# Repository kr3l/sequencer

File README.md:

ESP32 + TL074

the TL074 opamp is fed with -12 and +12V

GPIO25 -> pin3 of opamp
5.6kOhm + 1kOhm precision trimmer between pin 1 and 2 of opamp (feedback resistor)
10kOhm resistor between pin 2 and GND
-> opamp gain 1 + 5.6/10 -> 1.56
-> output max goes from 3.3V to 5.148V

100nF between pin 1 and GND

precision trimmer calibrated so the max outputted voltage on DAC results in exactly 5V

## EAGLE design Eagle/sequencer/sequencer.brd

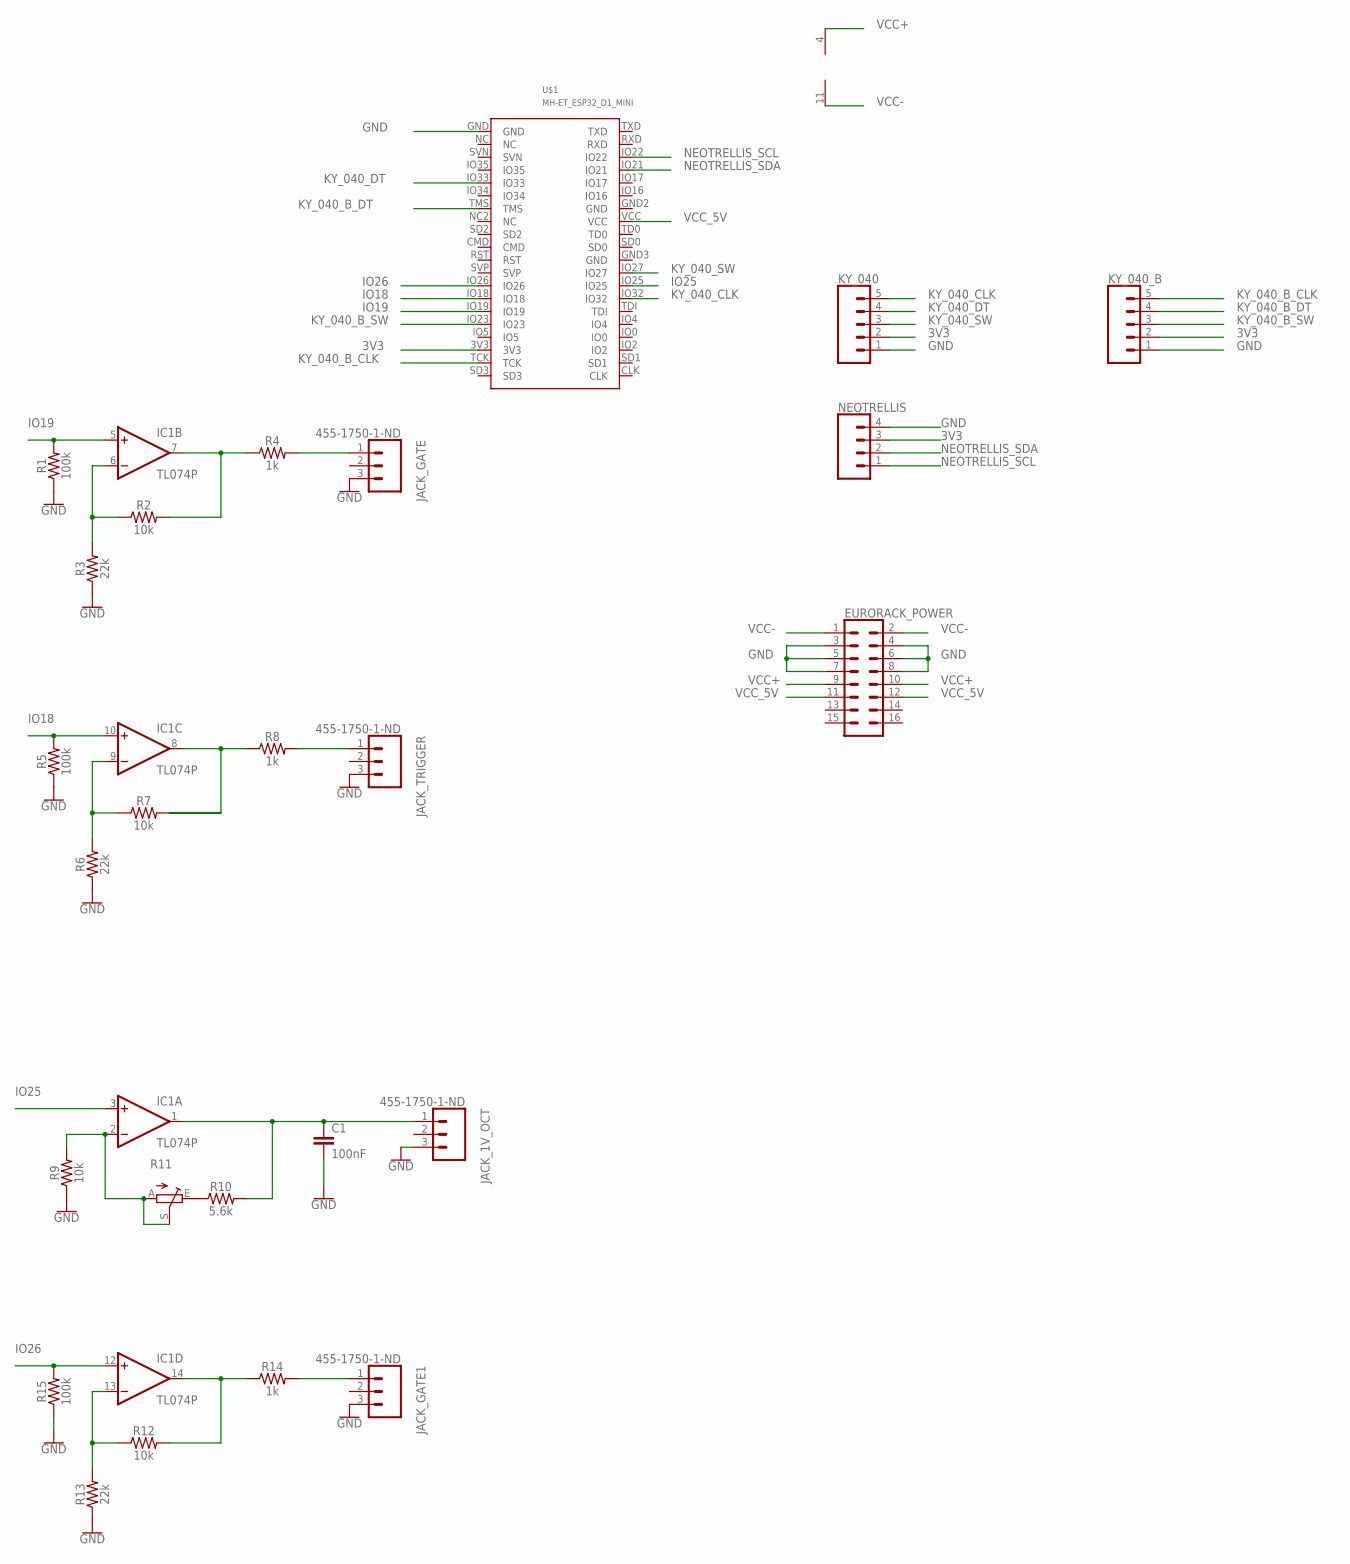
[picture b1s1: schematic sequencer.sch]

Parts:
C1: 100nF; C050-035X075
EURORACK_POWER: CONN_08X2_SHROUD; 2X8-SHROUDED_LOCK
IC1: TL074P; DIL14
JACK_1V_OCT: 455-1750-1-ND; 1X03
JACK_GATE, JACK_GATE1: 455-1750-1-ND; 1X03
JACK_TRIGGER: 455-1750-1-ND; 1X03
KY_040, KY_040_B: CONN_05; 1X05
NEOTRELLIS: CONN_04PTH; 1X04
R1, R5, R15: 100k; AXIAL-0.1
R2, R7, R9, R12: 10k; AXIAL-0.1
R3, R6, R13: 22k; AXIAL-0.1
R4, R8, R14: 1k; AXIAL-0.1
R10: 5.6k; AXIAL-0.1
R11: TRIM_EU-B64W; B64W
U$1: MH-ET_ESP32_D1_MINI

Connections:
3V3: KY_040.2, KY_040_B.2, NEOTRELLIS.3, U$1.3V3
GND: C1.2, EURORACK_POWER.3, EURORACK_POWER.4, EURORACK_POWER.5, EURORACK_POWER.6, EURORACK_POWER.7, EURORACK_POWER.8, JACK_1V_OCT.3, JACK_GATE.3, JACK_GATE1.3, JACK_TRIGGER.3, KY_040.1, KY_040_B.1, NEOTRELLIS.4, R1.P$1 (1), R3.P$1 (1), R5.P$1 (1), R6.P$1 (1), R9.P$1 (1), R13.P$1 (1), R15.P$1 (1), U$1.GND
IO18: IC1.10 (+IN), R5.P$2 (2), U$1.IO18
IO19: IC1.5 (+IN), R1.P$2 (2), U$1.IO19
IO25: IC1.3 (+IN), U$1.IO25
IO26: IC1.12 (+IN), R15.P$2 (2), U$1.IO26
KY_040_B_CLK: KY_040_B.5, U$1.TCK
KY_040_B_DT: KY_040_B.4, U$1.TMS
KY_040_B_SW: KY_040_B.3, U$1.IO23
KY_040_CLK: KY_040.5, U$1.IO32
KY_040_DT: KY_040.4, U$1.IO33
KY_040_SW: KY_040.3, U$1.IO27
unnamed: IC1.6 (-IN), R2.P$1 (1), R3.P$2 (2)
unnamed: IC1.7 (OUT), R2.P$2 (2), R4.P$1 (1)
unnamed: JACK_GATE.1, R4.P$2 (2)
unnamed: IC1.9 (-IN), R6.P$2 (2), R7.P$1 (1)
unnamed: IC1.8 (OUT), R8.P$1 (1)
unnamed: JACK_TRIGGER.1, R8.P$2 (2)
unnamed: IC1.13 (-IN), R12.P$1 (1), R13.P$2 (2)
unnamed: C1.1, IC1.1 (OUT), JACK_1V_OCT.1, R10.P$2 (2)
unnamed: R10.P$1 (1), R11.E
unnamed: IC1.2 (-IN), R9.P$2 (2), R11.A, R11.S
unnamed: IC1.14 (OUT), R12.P$2 (2), R14.P$1 (1)
unnamed: JACK_GATE1.1, R14.P$2 (2)
NEOTRELLIS_SCL: NEOTRELLIS.1, U$1.IO22
NEOTRELLIS_SDA: NEOTRELLIS.2, U$1.IO21
VCC+: EURORACK_POWER.9, EURORACK_POWER.10, IC1.4 (V+)
VCC-: EURORACK_POWER.1, EURORACK_POWER.2, IC1.11 (V-)
VCC_5V: EURORACK_POWER.11, EURORACK_POWER.12, U$1.VCC

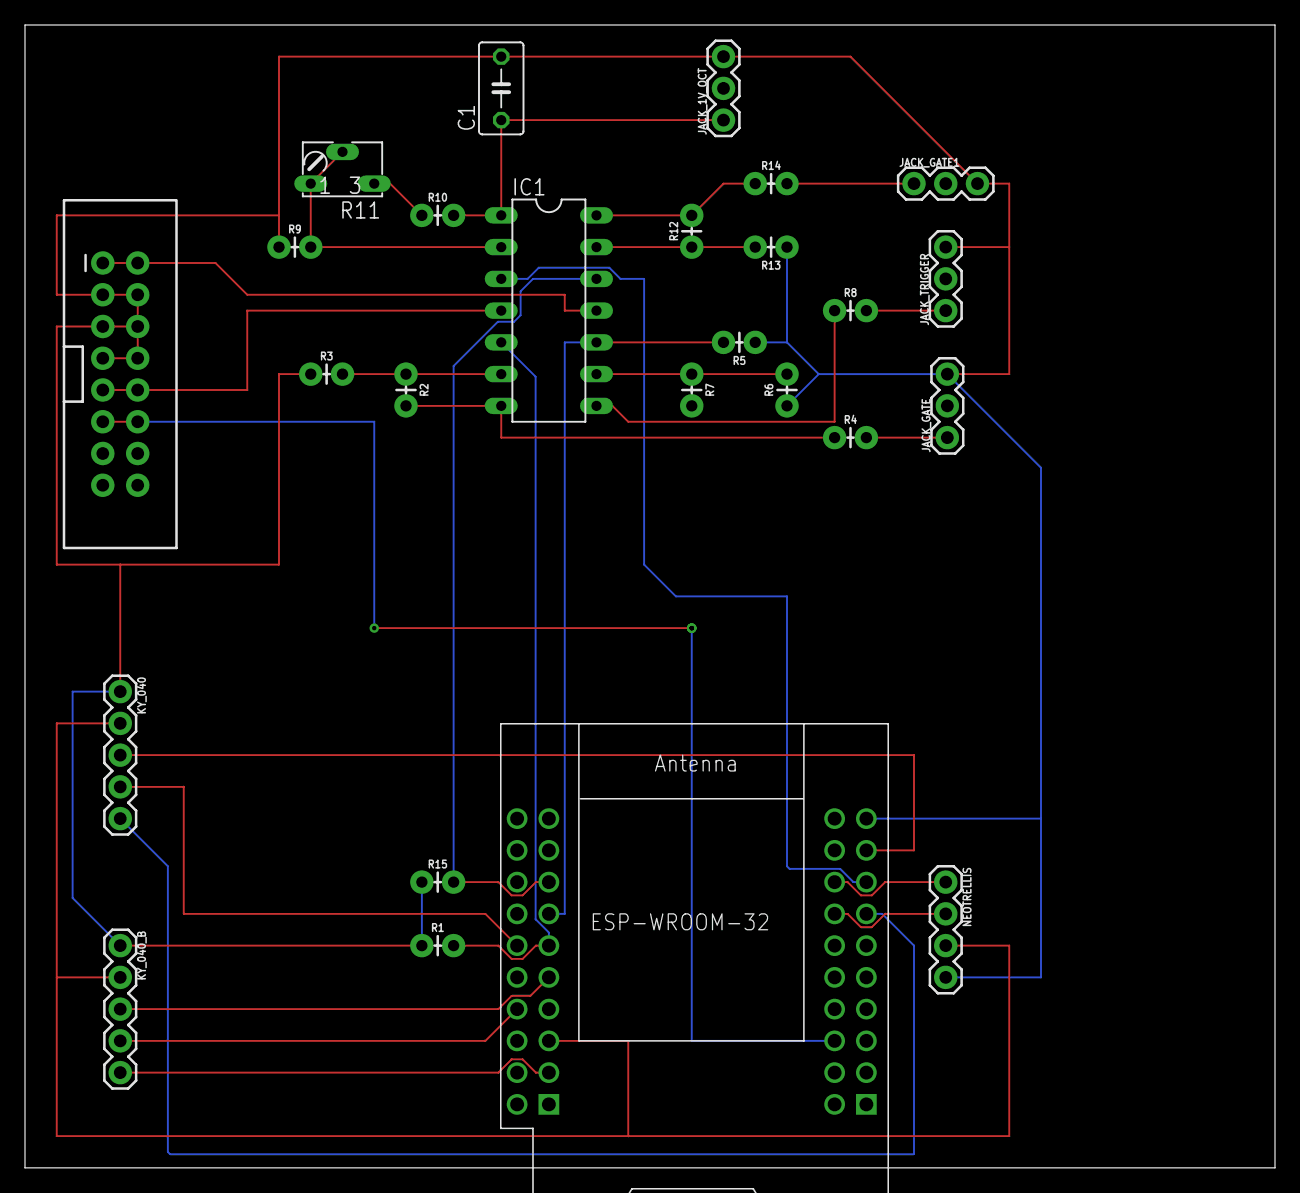
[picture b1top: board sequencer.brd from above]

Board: 2 copper layers, 100.0 x 91.4 mm, 26 parts (0 on the bottom side), 29 nets.

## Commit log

2025-05-24 initial code
2025-05-24 add precision trimmer
2025-05-24 shift notes
2025-08-17 add neotrellis, program notes
2025-08-17 fusion 360 round plate and tray
2025-08-22 move some code into classes
2025-08-22 move more code into classes
2025-08-23 move melodies to a header
2025-08-23 changed interface to a mode button, pitch, duty cycle, on/off can be set
2025-08-23 dim led when not active but programmed and gate on
2025-08-23 velocity mode + actually write gate and trigger outputs
2025-09-20 encoders instead of pot (untested)
2025-09-20 Revert "encoders instead of pot (untested)"
    This reverts commit 05debf08ba5b22f98a5a2d6460360932c0ab7ab3.
2025-09-20 working with other encoder lib
2025-09-25 follow advise from library readme and set filter high
2025-09-25 cast to float
2025-09-25 when programming pitch value, start from previous value
2025-09-25 fix remember last tempo
2025-09-25 cad files for eurorack panel sequencer
2025-09-25 Eagle schematic and board layout
2025-09-25 display, render mode and pitch
2025-09-26 let one encoder tick move up/down one note
2025-09-26 save programmed values to preferences
2025-09-26 save tempo to prefs as well
2025-09-26 display tempo and duty as well while changing
2025-09-26 stepcount mode + playout fix
2025-09-26 now that we have gate and trigger, no longer set dac out to 0

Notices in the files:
parts and their libraries:
SparkFun-Resistors: Licensing: Creative Commons ShareAlike 4.0 International - https://creativecommons.org/licenses/by-sa/4.0
